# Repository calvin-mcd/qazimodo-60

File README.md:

# qazimodo 60

The qazimodo 60 is a collaboration with Soyo. It is a qaz-like keyboard pcb featuring both a number row and cluster all within a 60% formfactor while offering basekit support. It is designed to fit both traymount as well as most common O-ring mount cases.

The project takes inspiration and reference from other projects such as tominabox1 and whydobearsxplod's [QAZ](https://www.cbkbd.com/product/qaz), kkatano#2078's [Bakaneko](https://github.com/kkatano/bakeneko-60), evyd13's [plain60](https://github.com/evyd13/plain60-flex-edition) and dede and Olivia's [SST60](https://github.com/dededecline/SST60).

## Layout

[Link](http://www.keyboard-layout-editor.com/\#/gists/fcfe4194cc3239e0c420215ebe271a12)
  
## Todo
- [ ] update silkscreen for revision
- [ ] order revision & test firmware
- [ ] confirm case compatibility

## Disclaimer

Please note that this project is a work in progress with no guarantees of a working outcome. No-one involved in this project is responsible for any usage issues that may arise. Order at your own risk. Support will not be provided but pull requests will be reviewed and possibly accepted.

## License

Shield: [![CC BY-NC-SA 4.0][cc-by-nc-sa-shield]][cc-by-nc-sa]

This work is licensed under a
[Creative Commons Attribution-NonCommercial-ShareAlike 4.0 International License][cc-by-nc-sa].

[![CC BY-NC-SA 4.0][cc-by-nc-sa-image]][cc-by-nc-sa]

[cc-by-nc-sa]: http://creativecommons.org/licenses/by-nc-sa/4.0/
[cc-by-nc-sa-image]: https://licensebuttons.net/l/by-nc-sa/4.0/88x31.png
[cc-by-nc-sa-shield]: https://img.shields.io/badge/License-CC%20BY--NC--SA%204.0-lightgrey.svg
  
## Credits

Any questions, contact Soyo & Calvin0563 on Discord.

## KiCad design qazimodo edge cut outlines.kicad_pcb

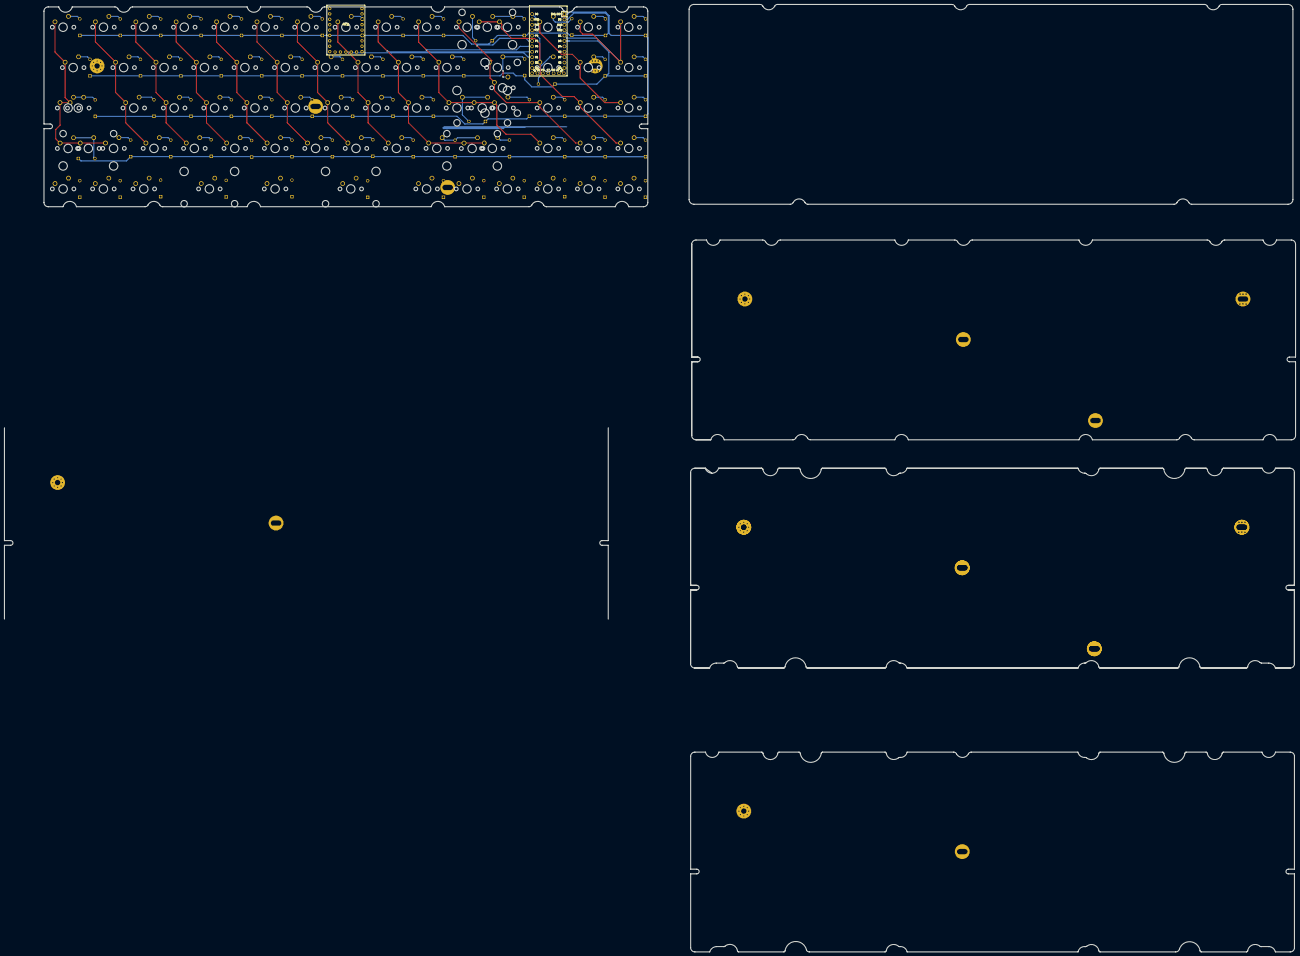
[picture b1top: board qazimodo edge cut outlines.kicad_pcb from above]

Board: 2 copper layers, 284.7 x 94.2 mm, 147 parts (1 on the bottom side), 89 nets.

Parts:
D1, D2, D3, D4, D5, D6, D7, D8, D9, D10, D11, D12, D13, D14, D15, D16, D17, D18, D19, D20, D21, D22, D23, D24, D25, D26, D27, D28, D29, D30, D31, D32, D33, D34, D35, D36, D37, D38, D39, D40, D41, D42, D43, D44, D45, D46, D47, D48, D49, D50, D51, D52, D53, D54, D55, D56, D57, D58, D59, D60, D61, D62, D63, D65, D66, D68, D70, D71, D72: D_Small; Diode-Hybrid-Back
H1: PCB Outline; L60 Outline
MX1, MX2, MX3, MX4, MX5, MX6, MX7, MX8, MX9, MX10, MX11, MX12, MX13, MX14, MX15, MX17, MX18, MX19, MX20, MX21, MX22, MX23, MX24, MX25, MX27, MX28, MX29, MX31, MX32, MX33, MX34, MX35, MX36, MX37, MX38, MX39a1, MX40, MX41, MX42, MX43b1, MX44, MX45, MX46, MX47, MX48, MX49, MX50, MX51, MX52, MX53, MX54, MX55, MX56, MX57, MX59, MX61, MX62, MX63, MX64, MX65, MX66: MX-NoLED; MXOnly-1U-NoLED
MX12a1: MX-NoLED; MXOnly-2U-NoLED
MX16, MX26: MX-NoLED; MXOnly-1.5U-NoLED
MX26a1: MX-NoLED; MXOnly-ISO-ReversedStabilizers-NoLED
MX30, MX51a1: MX-NoLED; MXOnly-1.75U-NoLED
MX30a1, MX39b1, MX43a1: MX-NoLED; MXOnly-1.25U-NoLED
MX39, MX58: MX-NoLED; MXOnly-2.25U-ReversedStabilizers-NoLED
MX43: MX-NoLED; MXOnly-2.25U-NoLED
MX51b1: MX-NoLED; MXOnly-2.75U-NoLED
MX60: MX-NoLED; MXOnly-2.75U-ReversedStabilizers-NoLED
RZ1: RP2040-Zero
U1: Elite-C

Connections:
COL0: MX1.1 (COL), MX16.1 (COL), MX30.1 (COL), MX30a1.1 (COL), MX43.1 (COL), MX43a1.1 (COL), MX43b1.1 (COL), MX55.1 (COL)
COL1: MX2.1 (COL), MX17.1 (COL), MX31.1 (COL), MX44.1 (COL), MX56.1 (COL), U1.16 (15/PB1)
COL2: MX3.1 (COL), MX18.1 (COL), MX32.1 (COL), MX45.1 (COL), MX57.1 (COL), U1.17 (A0/PF7)
COL3: MX4.1 (COL), MX19.1 (COL), MX33.1 (COL), MX46.1 (COL), MX58.1 (COL), U1.18 (A1/PF6)
COL4: MX5.1 (COL), MX20.1 (COL), MX34.1 (COL), MX47.1 (COL), MX59.1 (COL), U1.19 (A2/PF5)
COL5: MX6.1 (COL), MX21.1 (COL), MX35.1 (COL), MX48.1 (COL), MX60.1 (COL), U1.20 (A3/PF4)
COL6: MX7.1 (COL), MX22.1 (COL), MX36.1 (COL), MX49.1 (COL), MX61.1 (COL)
COL7: MX8.1 (COL), MX23.1 (COL), MX37.1 (COL), MX50.1 (COL), MX62.1 (COL)
COL8: MX9.1 (COL), MX24.1 (COL), MX38.1 (COL), MX51.1 (COL), MX51a1.1 (COL), MX51b1.1 (COL), MX63.1 (COL)
COL9: MX10.1 (COL), MX25.1 (COL), MX39.1 (COL), MX39a1.1 (COL), MX39b1.1 (COL), MX52.1 (COL), MX64.1 (COL)
COL10: MX11.1 (COL), MX26.1 (COL), MX26a1.1 (COL), MX40.1 (COL), MX53.1 (COL), MX65.1 (COL)
COL11: MX12.1 (COL), MX12a1.1 (COL), MX27.1 (COL), MX41.1 (COL), MX54.1 (COL), MX66.1 (COL)
COL12: MX13.1 (COL), MX28.1 (COL), MX42.1 (COL), U1.24 (B0)
COL13: MX14.1 (COL), MX15.1 (COL), MX29.1 (COL), U1.5 (2/PD1)
GND: H1.1, RZ1.23 (GND), U1.3 (GND), U1.4 (GND), U1.23 (GND)
unnamed: D1.2 (A), MX1.2 (ROW)
unnamed: D2.2 (A), MX16.2 (ROW)
unnamed: D3.2 (A), MX30.2 (ROW), MX30a1.2 (ROW)
unnamed: D4.2 (A), MX43.2 (ROW), MX43a1.2 (ROW)
unnamed: D5.2 (A), MX55.2 (ROW)
unnamed: D6.2 (A), MX2.2 (ROW)
unnamed: D7.2 (A), MX17.2 (ROW)
unnamed: D8.2 (A), MX31.2 (ROW)
unnamed: D9.2 (A), MX44.2 (ROW)
unnamed: D10.2 (A), MX56.2 (ROW)
unnamed: D11.2 (A), MX3.2 (ROW)
unnamed: D12.2 (A), MX18.2 (ROW)
unnamed: D13.2 (A), MX32.2 (ROW)
unnamed: D14.2 (A), MX45.2 (ROW)
unnamed: D15.2 (A), MX57.2 (ROW)
unnamed: D16.2 (A), MX4.2 (ROW)
unnamed: D17.2 (A), MX19.2 (ROW)
unnamed: D18.2 (A), MX33.2 (ROW)
unnamed: D19.2 (A), MX46.2 (ROW)
unnamed: D20.2 (A), MX58.2 (ROW)
unnamed: D21.2 (A), MX5.2 (ROW)
unnamed: D22.2 (A), MX20.2 (ROW)
unnamed: D23.2 (A), MX34.2 (ROW)
unnamed: D24.2 (A), MX47.2 (ROW)
unnamed: D25.2 (A), MX59.2 (ROW)
unnamed: D26.2 (A), MX6.2 (ROW)
unnamed: D27.2 (A), MX21.2 (ROW)
unnamed: D28.2 (A), MX35.2 (ROW)
unnamed: D29.2 (A), MX48.2 (ROW)
unnamed: D30.2 (A), MX60.2 (ROW)
unnamed: D31.2 (A), MX7.2 (ROW)
unnamed: D32.2 (A), MX22.2 (ROW)
unnamed: D33.2 (A), MX36.2 (ROW)
unnamed: D34.2 (A), MX49.2 (ROW)
unnamed: D35.2 (A), MX61.2 (ROW)
unnamed: D36.2 (A), MX8.2 (ROW)
unnamed: D37.2 (A), MX23.2 (ROW)
unnamed: D38.2 (A), MX37.2 (ROW)
unnamed: D39.2 (A), MX50.2 (ROW)
unnamed: D40.2 (A), MX62.2 (ROW)
unnamed: D41.2 (A), MX9.2 (ROW)
unnamed: D42.2 (A), MX24.2 (ROW)
unnamed: D43.2 (A), MX38.2 (ROW)
unnamed: D44.2 (A), MX51.2 (ROW), MX51b1.2 (ROW)
unnamed: D45.2 (A), MX63.2 (ROW)
unnamed: D46.2 (A), MX10.2 (ROW)
unnamed: D47.2 (A), MX25.2 (ROW)
unnamed: D48.2 (A), MX39.2 (ROW), MX39a1.2 (ROW)
unnamed: D49.2 (A), MX52.2 (ROW)
unnamed: D50.2 (A), MX64.2 (ROW)
unnamed: D51.2 (A), MX11.2 (ROW)
unnamed: D52.2 (A), MX26.2 (ROW), MX26a1.2 (ROW)
unnamed: D53.2 (A), MX40.2 (ROW)
unnamed: D54.2 (A), MX53.2 (ROW)
unnamed: D55.2 (A), MX65.2 (ROW)
unnamed: D56.2 (A), MX12.2 (ROW), MX12a1.2 (ROW)
unnamed: D57.2 (A), MX27.2 (ROW)
unnamed: D58.2 (A), MX41.2 (ROW)
unnamed: D59.2 (A), MX54.2 (ROW)
unnamed: D60.2 (A), MX66.2 (ROW)
unnamed: D61.2 (A), MX13.2 (ROW)
unnamed: D62.2 (A), MX28.2 (ROW)
unnamed: D63.2 (A), MX42.2 (ROW)
unnamed: D65.2 (A), MX14.2 (ROW)
unnamed: D66.2 (A), MX29.2 (ROW)
unnamed: D68.2 (A), MX15.2 (ROW)
unnamed: D70.2 (A), MX43b1.2 (ROW)
unnamed: D71.2 (A), MX51a1.2 (ROW)
unnamed: D72.2 (A), MX39b1.2 (ROW)
ROW0: D1.1 (K), D6.1 (K), D11.1 (K), D16.1 (K), D21.1 (K), D26.1 (K), D31.1 (K), D36.1 (K), D41.1 (K), D46.1 (K), D51.1 (K), D56.1 (K), D61.1 (K), D65.1 (K), U1.2 (RX1/PD2)
ROW1: D2.1 (K), D7.1 (K), D12.1 (K), D17.1 (K), D22.1 (K), D27.1 (K), D32.1 (K), D37.1 (K), D42.1 (K), D47.1 (K), D52.1 (K), D57.1 (K), D62.1 (K), D66.1 (K), U1.6 (3/PD0)
ROW2: D3.1 (K), D8.1 (K), D13.1 (K), D18.1 (K), D23.1 (K), D28.1 (K), D33.1 (K), D38.1 (K), D43.1 (K), D48.1 (K), D53.1 (K), D58.1 (K), D63.1 (K), D68.1 (K), D72.1 (K), U1.1 (TX0/PD3)
ROW3: D4.1 (K), D9.1 (K), D14.1 (K), D19.1 (K), D24.1 (K), D29.1 (K), D34.1 (K), D39.1 (K), D44.1 (K), D49.1 (K), D54.1 (K), D59.1 (K), D70.1 (K), D71.1 (K), U1.28 (F1)
ROW4: D5.1 (K), D10.1 (K), D15.1 (K), D20.1 (K), D25.1 (K), D30.1 (K), D35.1 (K), D40.1 (K), D45.1 (K), D50.1 (K), D55.1 (K), D60.1 (K), U1.29 (F0)

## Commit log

2023-03-04 initialise
2023-03-05 front silkscreen
2023-03-05 project clean up, readme update
2023-03-06 fresh production files
2023-03-10 backups
2023-03-13 backup
2023-03-26 matrix issues deteced and fixed, needs new silkscreen
2023-03-26 reset pins corrected
2023-03-28 small clean up
2023-04-01 revision work
2023-04-07 moved qazi proto to onhold folder
2023-04-13 added firmware
2023-04-24 fresh svgs
2023-05-29 updated BOM with correct parts
2023-07-10 fresh svg files
2023-09-12 update project
2023-10-08 updated kle
2024-03-14 changed MCU to STM
2024-06-07 revision wip
2024-08-05 revision
